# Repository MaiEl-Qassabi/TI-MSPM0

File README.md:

A Two layer PCB design  for Texas Instruments MSPM0-based hardware (USB, power, MCU, peripherals). guided by Phil’s Lab
THE VIDEO LINK: https://www.youtube.com/watch?v=O-zNn5k5Bn4

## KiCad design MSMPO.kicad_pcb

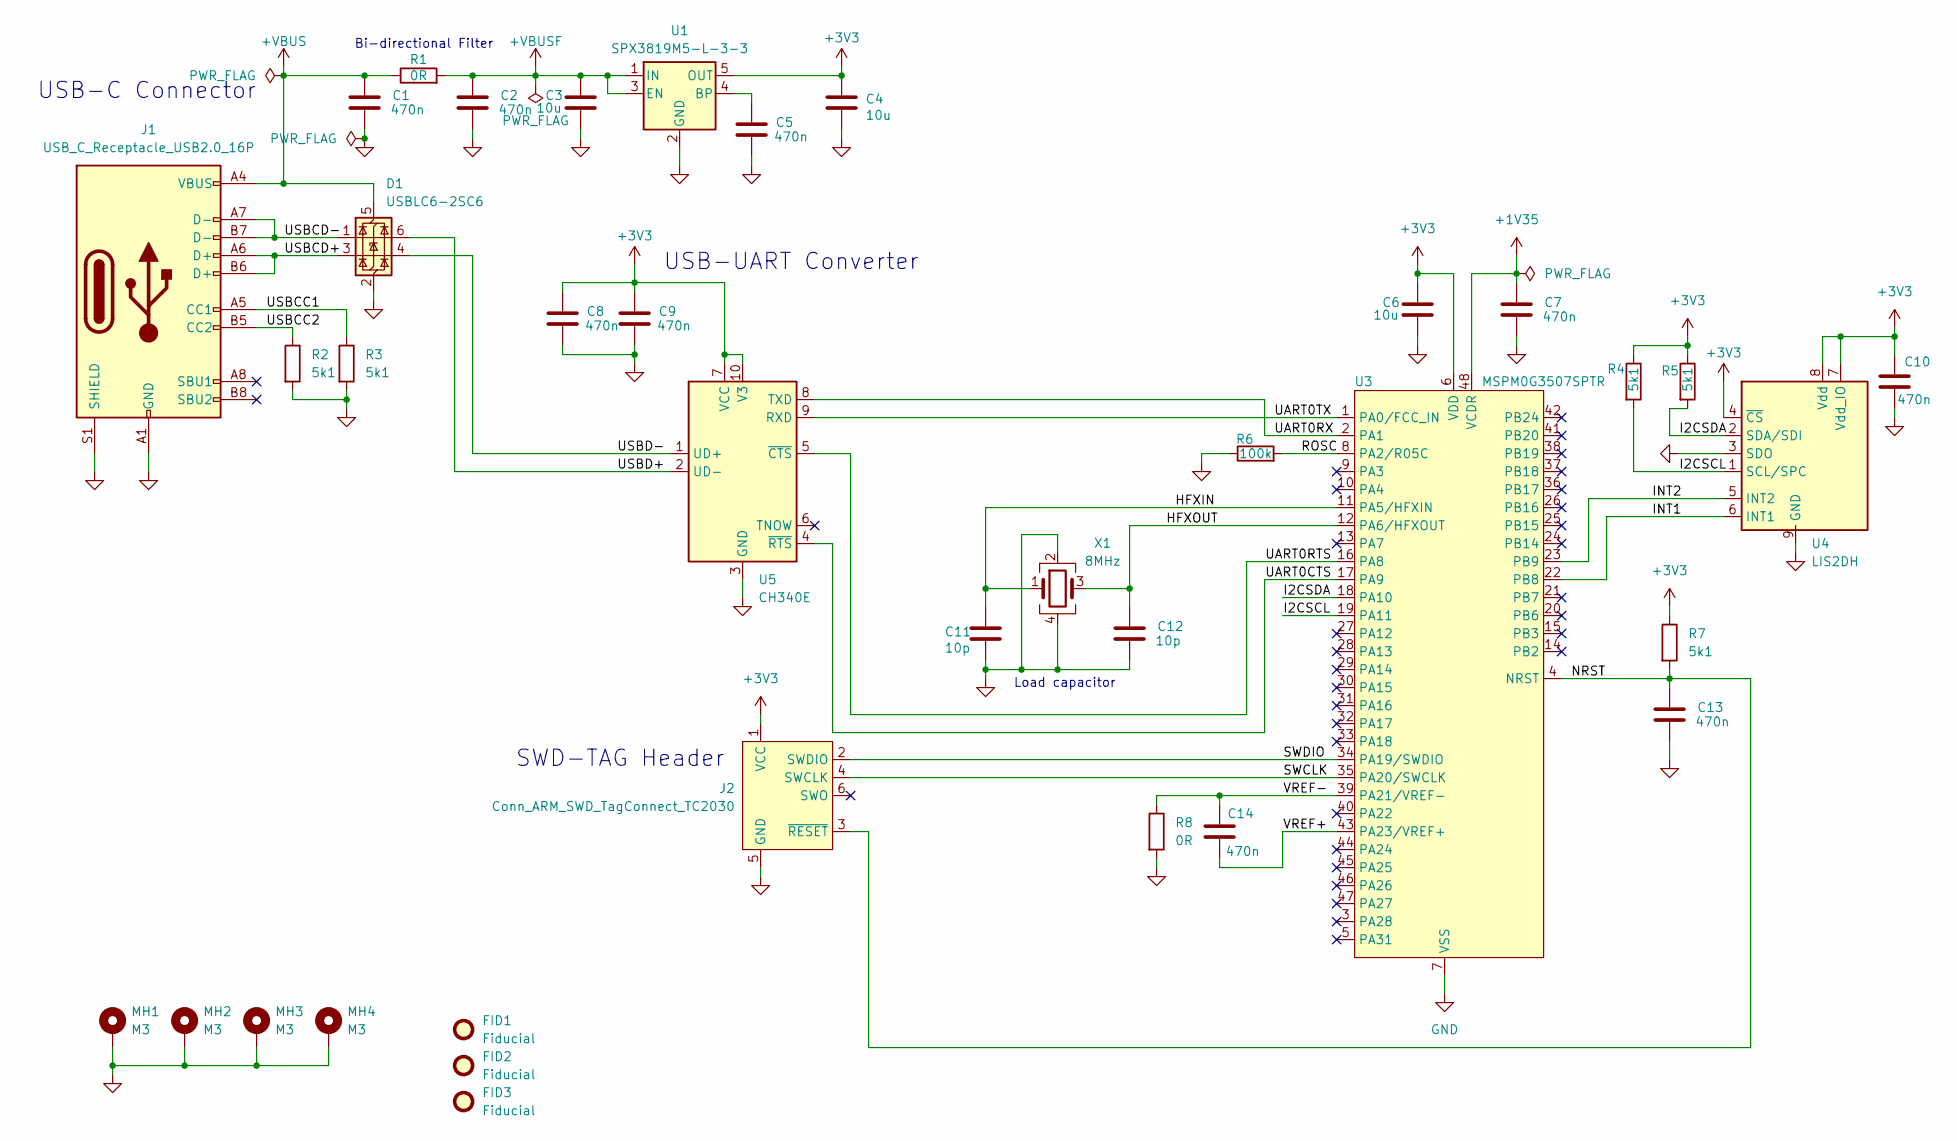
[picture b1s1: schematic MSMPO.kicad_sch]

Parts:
C1, C2, C5, C7, C8, C9, C10, C13, C14: 470n; C_0603_1608Metric
C3, C4, C6: 10u; C_0805_2012Metric
C11, C12: 10p; C_0603_1608Metric
D1: USBLC6-2SC6; SOT-23-6
FID1, FID2, FID3: Fiducial; Fiducial_1mm_Mask2mm
J1: USB_C_Receptacle_USB2.0_16P; USB_C_Receptacle_GCT_USB4105-xx-A_16P_TopMnt_Horizontal
J2: Conn_ARM_SWD_TagConnect_TC2030; Tag-Connect_TC2030-IDC-FP_2x03_P1.27mm_Vertical
MH1, MH2, MH3, MH4: M3; MountingHole_3mm_Pad_Via
R1, R8: 0R; R_0603_1608Metric
R2, R3, R4, R5, R7: 5k1; R_0603_1608Metric
R6: 100k; R_0603_1608Metric
U1: SPX3819M5-L-3-3; SOT-23-5
U3: MSPM0G3507SPTR; LQFP-48_7x7mm_P0.5mm
U4: LIS2DH; LGA-14_2x2mm_P0.35mm_LayoutBorder3x4y
U5: CH340E; MSOP-10_3x3mm_P0.5mm
X1: 8MHz; Crystal_SMD_3225-4Pin_3.2x2.5mm

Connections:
+1V35: C7.1, U3.48 (VCDR)
+3V3: C4.1, C6.1, C8.1, C9.1, C10.1, J2.1 (VCC), R4.1, R5.1, R7.1, U1.5 (OUT), U3.6 (VDD), U4.4 (~CS), U4.7 (Vdd_IO), U4.8 (Vdd), U5.7 (VCC), U5.10 (V3)
+VBUS: C1.1, D1.5 (VBUS), J1.A4 (VBUS), J1.A9 (VBUS), J1.B4 (VBUS), J1.B9 (VBUS), R1.1
+VBUSF: C2.1, C3.1, R1.2, U1.1 (IN), U1.3 (EN)
/HFXIN: C11.1, U3.11 (PA5/HFXIN), X1.1
/HFXOUT: C12.1, U3.12 (PA6/HFXOUT), X1.3
/I2CSCL: R4.2, U3.19 (PA11), U4.1 (SCL/SPC)
/I2CSDA: R5.2, U3.18 (PA10), U4.2 (SDA/SDI)
/INT1: U3.22 (PB8), U4.6 (INT1)
/INT2: U3.23 (PB9), U4.5 (INT2)
/NRST: C13.1, J2.3 (~RESET), R7.2, U3.4 (NRST)
/ROSC: R6.2, U3.8 (PA2/R05C)
/SWCLK: J2.4 (SWCLK), U3.35 (PA20/SWCLK)
/SWDIO: J2.2 (SWDIO), U3.34 (PA19/SWDIO)
/UART0CTS: U3.17 (PA9), U5.4 (~RTS)
/UART0RTS: U3.16 (PA8), U5.5 (~CTS)
/UART0RX: U3.2 (PA1), U5.8 (TXD)
/UART0TX: U3.1 (PA0/FCC_IN), U5.9 (RXD)
/USBCC1: J1.A5 (CC1), R3.1
/USBCC2: J1.B5 (CC2), R2.1
/USBCD+: D1.3 (I/O2), J1.A6 (D+), J1.B6 (D+)
/USBCD-: D1.1 (I/O1), J1.A7 (D-), J1.B7 (D-)
/USBD+: D1.6 (I/O1), U5.2 (UD-)
/USBD-: D1.4 (I/O2), U5.1 (UD+)
/VREF+: C14.2, U3.43 (PA23/VREF+)
/VREF-: C14.1, R8.1, U3.39 (PA21/VREF-)
GND: C1.2, C2.2, C3.2, C4.2, C5.2, C6.2, C7.2, C8.2, C9.2, C10.2, C11.2, C12.2, C13.2, D1.2 (GND), J1.A1 (GND), J1.A12 (GND), J1.B1 (GND), J1.B12 (GND), J1.S1 (SHIELD), J2.5 (GND), MH1.1, MH2.1, MH3.1, MH4.1, R2.2, R3.2, R6.1, R8.2, U1.2 (GND), U3.7 (VSS), U4.3 (SDO), U4.9 (GND), U4.10 (GND), U4.11 (GND), U4.12 (GND), U4.13 (GND), U4.14 (GND), U5.3 (GND), X1.2, X1.4
unnamed: C5.1, U1.4 (BP)

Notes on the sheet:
Load capacitor
SWD-TAG Header
USB-UART Converter
USB-C Connector
Bi-directional Filter

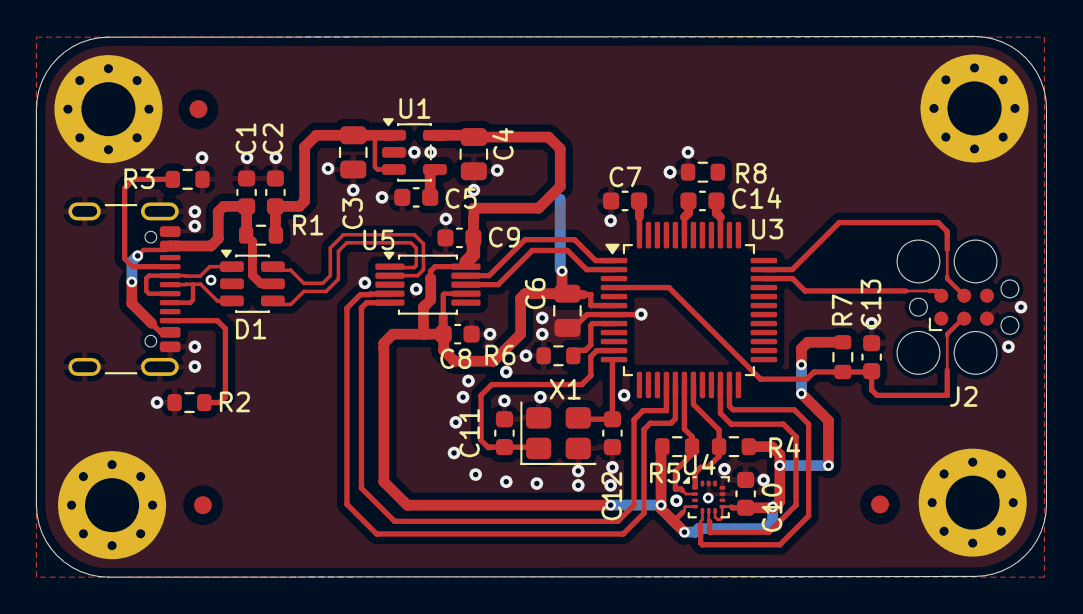
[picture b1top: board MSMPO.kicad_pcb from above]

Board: 2 copper layers, 56.1 x 30.0 mm, 37 parts (0 on the bottom side), 28 nets.
